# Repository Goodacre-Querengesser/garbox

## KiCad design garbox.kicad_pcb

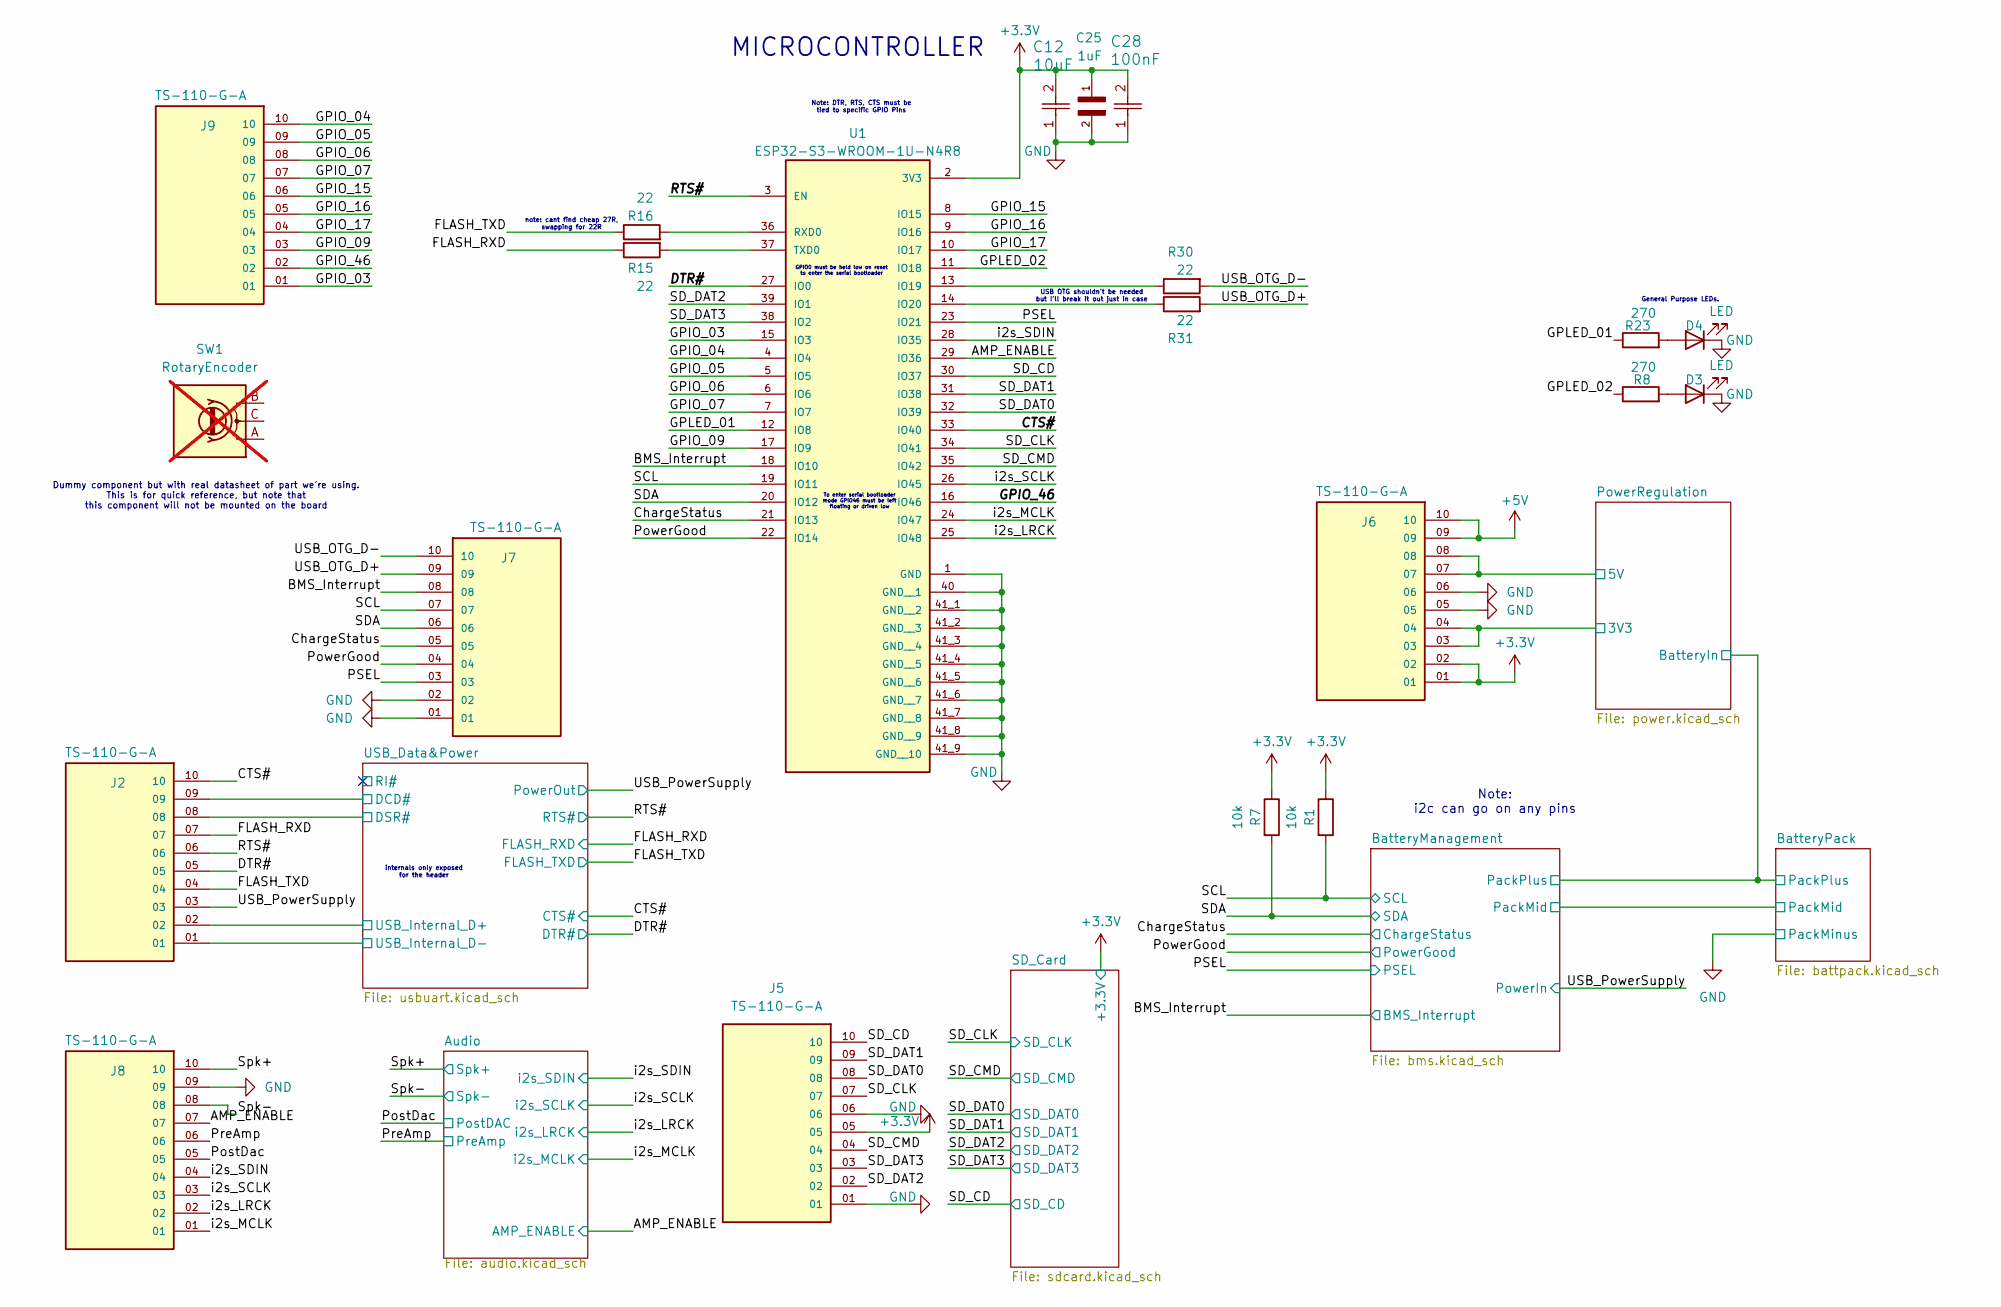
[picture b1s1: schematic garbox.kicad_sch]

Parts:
C12: 10uF; CAP_CL31_SAM; MPN C13585
C25: 1uF; CAPC3216X180N; MPN C1848
C28: 100nF; CAPC1005X55N; MPN C1525
D3, D4: LED; LED_0201_0603Metric; MPN C2286
J2, J5, J6, J7, J8, J9: TS-110-G-A; SAMTEC_TS-110-G-A; PARTREV R
R1, R7: 10k; R_0201_0603Metric; MPN C25804
R8, R23: 270; R_0201_0603Metric; MPN C22966
R15, R16, R30, R31: 22; R_0201_0603Metric; MPN C23345
SW1: RotaryEncoder; RotaryEncoder_Bourns_Horizontal_PEC09-2xxxF-Nxxxx; MPN C143788; not fitted
U1: ESP32-S3-WROOM-1U-N4R8; XCVR_ESP32-S3-WROOM-1U-N4R8; PARTREV v1.1

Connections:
+3.3V: C12.2, C25.1, C28.2, J5.05, J6.01, J6.02, R1.1, R7.1, U1.2 (3V3); also elsewhere on the board
+5V: J6.09, J6.10; also elsewhere on the board
/AMP_ENABLE: J8.07, U1.29 (IO36); also elsewhere on the board
/BMS_Interrupt: J7.08, U1.18 (IO10); also elsewhere on the board
/CTS#: J2.10, U1.33 (IO40); also elsewhere on the board
/ChargeStatus: J7.05, U1.21 (IO13); also elsewhere on the board
/DTR#: J2.05, U1.27 (IO0); also elsewhere on the board
/FLASH_RXD: J2.07, R15.1; also elsewhere on the board
/FLASH_TXD: J2.04, R16.1; also elsewhere on the board
/GPIO_03: J9.01, U1.15 (IO3)
/GPIO_04: J9.10, U1.4 (IO4)
/GPIO_05: J9.09, U1.5 (IO5)
/GPIO_06: J9.08, U1.6 (IO6)
/GPIO_07: J9.07, U1.7 (IO7)
/GPIO_09: J9.03, U1.17 (IO9)
/GPIO_15: J9.06, U1.8 (IO15)
/GPIO_16: J9.05, U1.9 (IO16)
/GPIO_17: J9.04, U1.10 (IO17)
/GPIO_46: J9.02, U1.16 (IO46)
/GPLED_01: R23.1, U1.12 (IO8)
/GPLED_02: R8.1, U1.11 (IO18)
/PSEL: J7.03, U1.23 (IO21); also elsewhere on the board
/PostDac: J8.05; also elsewhere on the board
/PowerGood: J7.04, U1.22 (IO14); also elsewhere on the board
/PowerRegulation/3V3: J6.03, J6.04; also elsewhere on the board
/PowerRegulation/5V: J6.07, J6.08; also elsewhere on the board
/PreAmp: J8.06; also elsewhere on the board
/RTS#: J2.06, U1.3 (EN); also elsewhere on the board
/SCL: J7.07, R1.2, U1.19 (IO11); also elsewhere on the board
/SDA: J7.06, R7.2, U1.20 (IO12); also elsewhere on the board
/SD_CD: J5.10, U1.30 (IO37); also elsewhere on the board
/SD_CLK: J5.07, U1.34 (IO41); also elsewhere on the board
/SD_CMD: J5.04, U1.35 (IO42); also elsewhere on the board
/SD_DAT0: J5.08, U1.32 (IO39); also elsewhere on the board
/SD_DAT1: J5.09, U1.31 (IO38); also elsewhere on the board
/SD_DAT2: J5.02, U1.39 (IO1); also elsewhere on the board
/SD_DAT3: J5.03, U1.38 (IO2); also elsewhere on the board
/Spk+: J8.10; also elsewhere on the board
/Spk-: J8.08; also elsewhere on the board
/USB_Data&Power/DCD#: J2.09; also elsewhere on the board
/USB_Data&Power/DSR#: J2.08; also elsewhere on the board
/USB_Data&Power/USB_D+: J2.02; also elsewhere on the board
/USB_Data&Power/USB_D-: J2.01; also elsewhere on the board
/USB_OTG_D+: J7.09, R31.2
/USB_OTG_D-: J7.10, R30.2
/USB_PowerSupply: J2.03; also elsewhere on the board
/i2s_LRCK: J8.02, U1.25 (IO48); also elsewhere on the board
/i2s_MCLK: J8.01, U1.24 (IO47); also elsewhere on the board
/i2s_SCLK: J8.03, U1.26 (IO45); also elsewhere on the board
/i2s_SDIN: J8.04, U1.28 (IO35); also elsewhere on the board
GND: C12.1, C25.2, C28.1, D3.1 (K), D4.1 (K), J5.01, J5.06, J6.05, J6.06, J7.01, J7.02, J8.09, U1.1 (GND), U1.40 (GND__1), U1.41_1 (GND__2), U1.41_2 (GND__3), U1.41_3 (GND__4), U1.41_4 (GND__5), U1.41_5 (GND__6), U1.41_6 (GND__7), U1.41_7 (GND__8), U1.41_8 (GND__9), U1.41_9 (GND__10), U1.41_10, U1.41_11, U1.41_12, U1.41_13, U1.41_14, U1.41_15, U1.41_16, U1.41_17, U1.41_18, U1.41_19, U1.41_20, U1.41_21; also elsewhere on the board
unnamed: D3.2 (A), R8.2
unnamed: D4.2 (A), R23.2
unnamed: R30.1, U1.13 (IO19)
unnamed: R31.1, U1.14 (IO20)
unnamed: R16.2, U1.36 (RXD0)
unnamed: R15.2, U1.37 (TXD0)

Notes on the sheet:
GPIO0 must be held low on reset to enter the serial bootloader
Note: DTR, RTS, CTS must be tied to specific GPIO Pins
internals only exposed for the header
note: cant find cheap 27R, swapping for 22R
Dummy component but with real datasheet of part we're using. This is for quick reference, but note that this component will not be mounted on the board
MICROCONTROLLER
Note: i2c can go on any pins
To enter serial bootloader mode GPIO46 must be left floating or driven low
USB OTG shouldn't be needed but I'll break it out just in case
General Purpose LEDs.

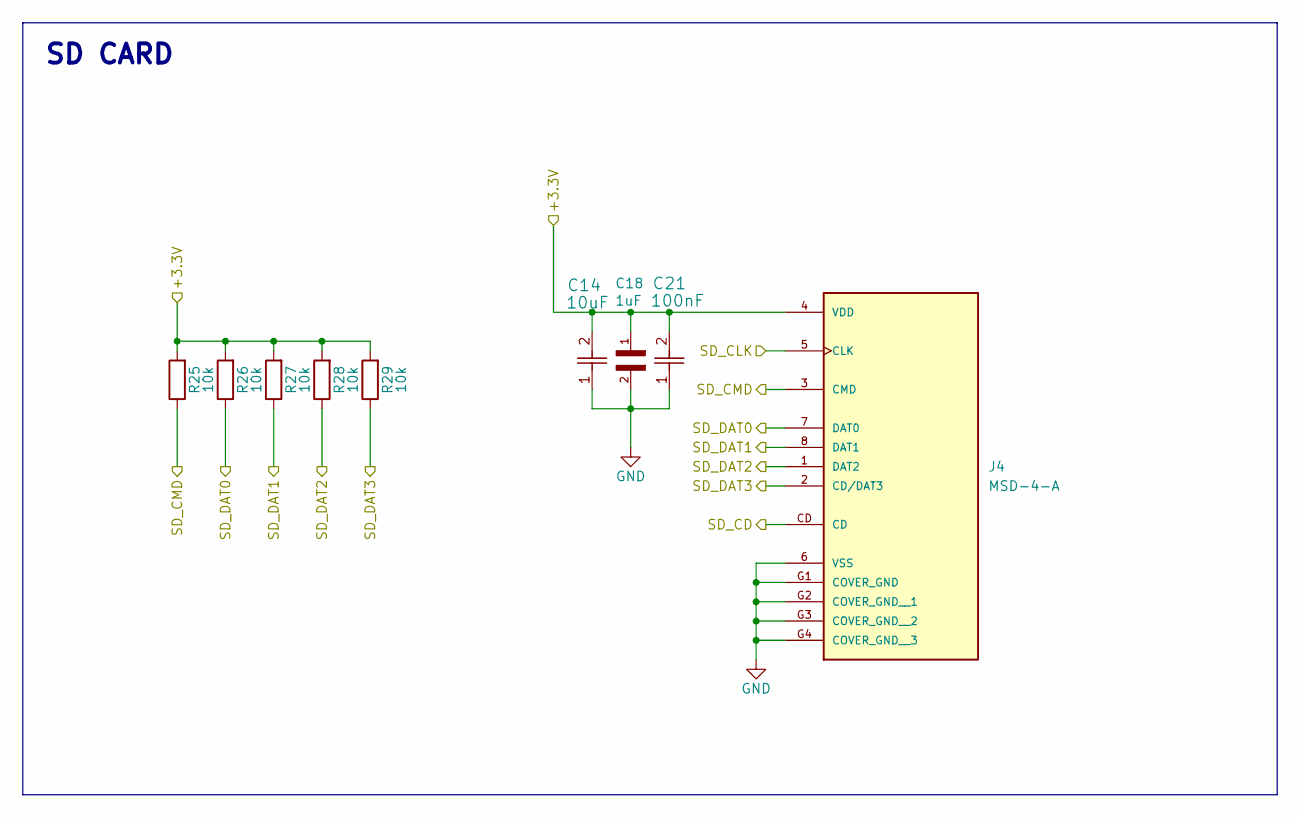
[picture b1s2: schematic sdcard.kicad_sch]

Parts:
C14: 10uF; CAP_CL31_SAM; MPN C13585
C18: 1uF; CAPC3216X180N; MPN C1848
C21: 100nF; CAPC1005X55N; MPN C1525
J4: MSD-4-A; CUI_MSD-4-A; PARTREV 1.0
R25, R26, R27, R28, R29: 10k; R_0201_0603Metric; MPN C25804

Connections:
+3.3V: C14.2, C18.1, C21.2, J4.4 (VDD), R25.2, R26.2, R27.2, R28.2, R29.2; also elsewhere on the board
/SD_CD: J4.CD; also elsewhere on the board
/SD_CLK: J4.5 (CLK); also elsewhere on the board
/SD_CMD: J4.3 (CMD), R25.1; also elsewhere on the board
/SD_DAT0: J4.7 (DAT0), R26.1; also elsewhere on the board
/SD_DAT1: J4.8 (DAT1), R27.1; also elsewhere on the board
/SD_DAT2: J4.1 (DAT2), R28.1; also elsewhere on the board
/SD_DAT3: J4.2 (CD/DAT3), R29.1; also elsewhere on the board
GND: C14.1, C18.2, C21.1, J4.6 (VSS), J4.G1 (COVER_GND), J4.G2 (COVER_GND__1), J4.G3 (COVER_GND__2), J4.G4 (COVER_GND__3); also elsewhere on the board

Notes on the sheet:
SD CARD

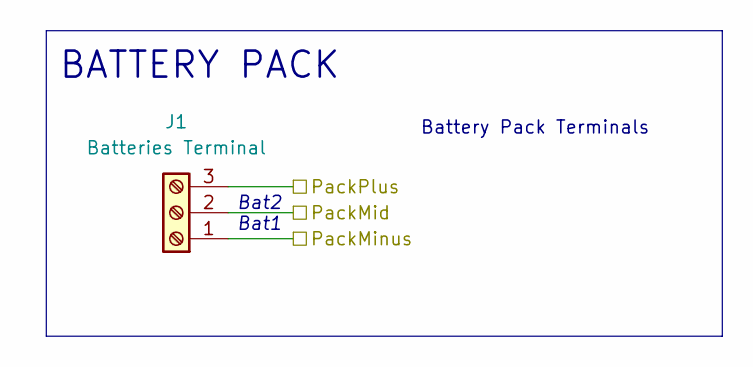
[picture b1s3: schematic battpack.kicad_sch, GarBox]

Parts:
J1: Batteries Terminal; TerminalBlock_bornier-3_P5.08mm

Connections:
/BatteryManagement/PackMid: J1.2; also elsewhere on the board
/BatteryManagement/PackPlus: J1.3; also elsewhere on the board
GND: J1.1; also elsewhere on the board

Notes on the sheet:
Battery Pack Terminals
BATTERY PACK
Bat2 Bat1

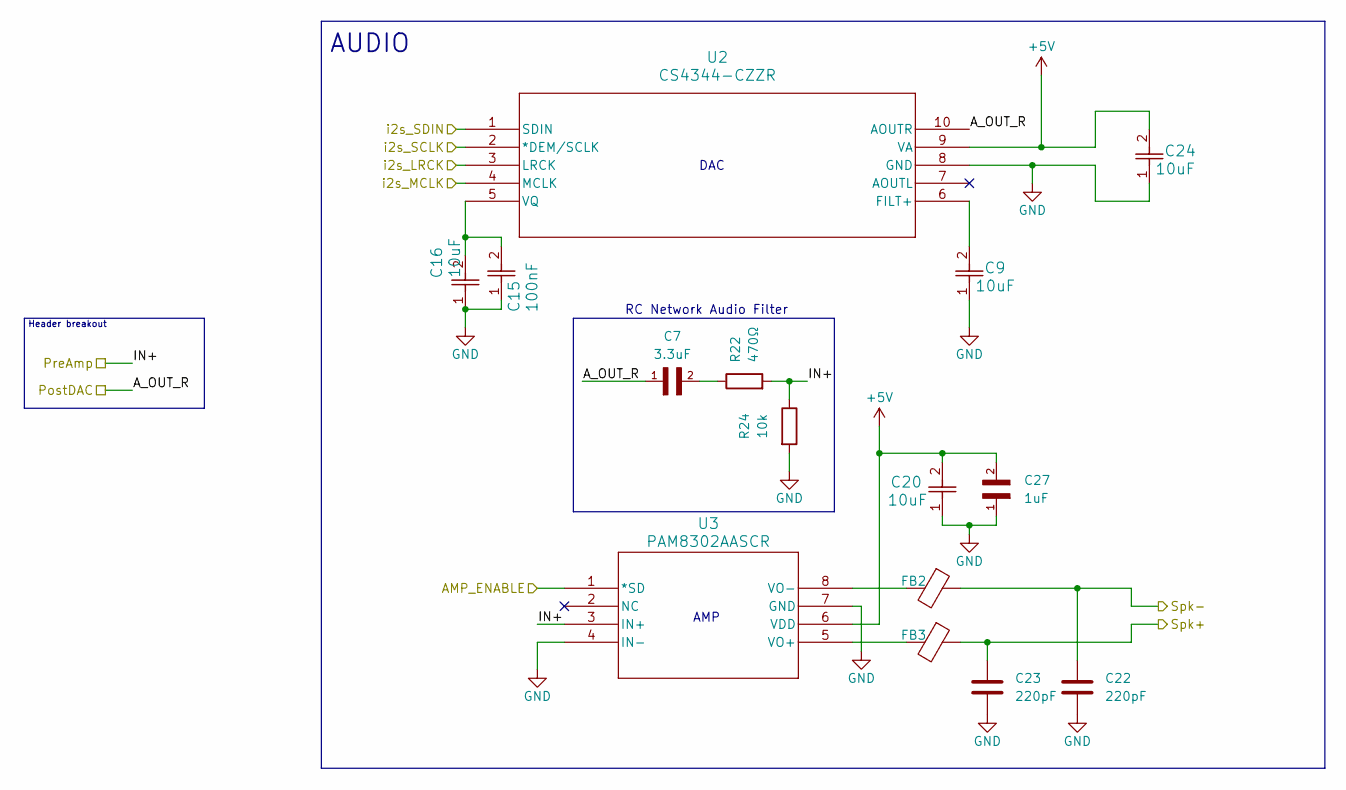
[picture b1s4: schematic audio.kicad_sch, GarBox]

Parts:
C7: 3.3uF; CAPC1608X90N; MPN C51412
C9, C16, C20, C24: 10uF; CAP_CL31_SAM; MPN C13585
C15: 100nF; CAPC1005X55N; MPN C1525
C22, C23: 220pF; C_0201_0603Metric; MPN C1603
C27: 1uF; CAPC3216X180N; MPN C1848
FB2, FB3: GZ1608D601TF; L_Sunlord_MWSA0603S; MPN C1002
R22: 470Ω; R_0603_1608Metric; MPN C23179
R24: 10k; R_0201_0603Metric; MPN C25804
U2: CS4344-CZZR; CIR_3TSSOP-10; MPN C2895053
U3: PAM8302AASCR; PAM8302AASCR_DIO; MPN C113367

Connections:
+5V: C20.2, C24.2, C27.2, U2.9 (VA), U3.6 (VDD); also elsewhere on the board
/AMP_ENABLE: U3.1 (*SD); also elsewhere on the board
/PostDac: C7.1, U2.10 (AOUTR); also elsewhere on the board
/PreAmp: R22.2, R24.1, U3.3 (IN+); also elsewhere on the board
/Spk+: C23.1, FB3.1; also elsewhere on the board
/Spk-: C22.1, FB2.1; also elsewhere on the board
/i2s_LRCK: U2.3 (LRCK); also elsewhere on the board
/i2s_MCLK: U2.4 (MCLK); also elsewhere on the board
/i2s_SCLK: U2.2 (*DEM/SCLK); also elsewhere on the board
/i2s_SDIN: U2.1 (SDIN); also elsewhere on the board
GND: C9.1, C15.1, C16.1, C20.1, C22.2, C23.2, C24.1, C27.1, R24.2, U2.8 (GND), U3.4 (IN-), U3.7 (GND); also elsewhere on the board
unnamed: C7.2, R22.1
unnamed: C9.2, U2.6 (FILT+)
unnamed: C15.2, C16.2, U2.5 (VQ)
unnamed: FB3.2, U3.5 (VO+)
unnamed: FB2.2, U3.8 (VO-)

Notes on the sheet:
AUDIO
Header breakout
AMP
DAC
RC Network Audio Filter

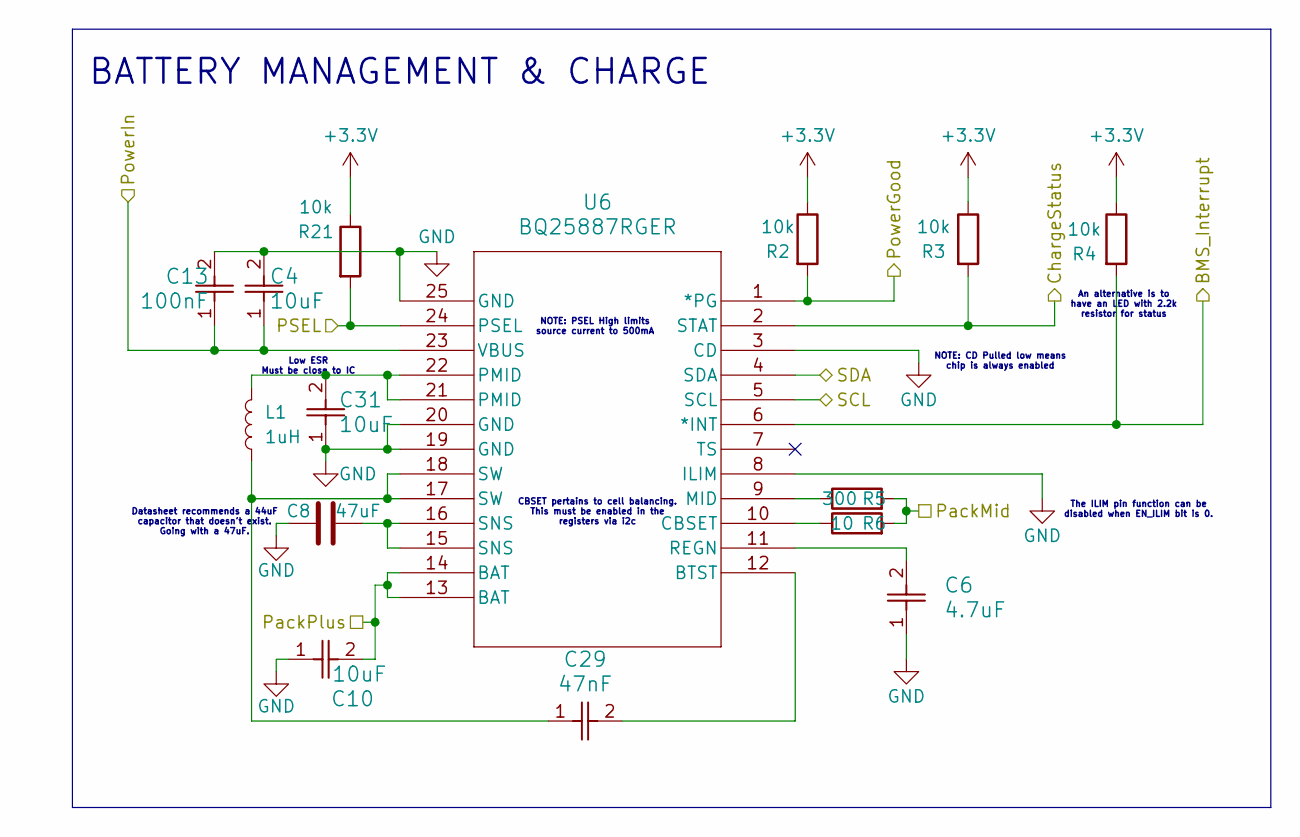
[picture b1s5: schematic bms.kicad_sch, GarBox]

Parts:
C4, C31: 10uF; CAP_CL21_SAM; MPN C15850
C6: 4.7uF; C_0805_2012Metric; MPN C1779
C8: 47uF; C_1206_3216Metric; MPN C96123
C10: 10uF; CAP_CL31_SAM; MPN C13585
C13: 100nF; CAPC1005X55N; MPN C1525
C29: 47nF; CAP_CL10_SAM; MPN C1622
L1: 1uH; L_Wuerth_WE-GF-1210; MPN C439775
R2, R3, R4, R21: 10k; R_0201_0603Metric; MPN C25804
R5: 300; R_0201_0603Metric; MPN C23025
R6: 10; R_2512_6332Metric; MPN C16861
U6: BQ25887RGER; VQFN24_RGE_TEX; MPN C2761614

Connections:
+3.3V: R2.1, R3.1, R4.1, R21.1; also elsewhere on the board
/BMS_Interrupt: R4.2, U6.6 (*INT); also elsewhere on the board
/BatteryManagement/PackMid: R5.2, R6.2; also elsewhere on the board
/BatteryManagement/PackPlus: C10.2, U6.13 (BAT), U6.14 (BAT); also elsewhere on the board
/ChargeStatus: R3.2, U6.2 (STAT); also elsewhere on the board
/PSEL: R21.2, U6.24 (PSEL); also elsewhere on the board
/PowerGood: R2.2, U6.1 (*PG); also elsewhere on the board
/SCL: U6.5 (SCL); also elsewhere on the board
/SDA: U6.4 (SDA); also elsewhere on the board
/USB_PowerSupply: C4.1, C13.1, U6.23 (VBUS); also elsewhere on the board
GND: C4.2, C6.1, C8.2, C10.1, C13.2, C31.1, U6.3 (CD), U6.8 (ILIM), U6.19 (GND), U6.20 (GND), U6.25 (GND); also elsewhere on the board
unnamed: C8.1, U6.15 (SNS), U6.16 (SNS)
unnamed: C29.1, L1.1, U6.17 (SW), U6.18 (SW)
unnamed: C31.2, L1.2, U6.21 (PMID), U6.22 (PMID)
unnamed: C29.2, U6.12 (BTST)
unnamed: R6.1, U6.10 (CBSET)
unnamed: R5.1, U6.9 (MID)
unnamed: C6.2, U6.11 (REGN)

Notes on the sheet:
BATTERY MANAGEMENT & CHARGE
NOTE: CD Pulled low means chip is always enabled
CBSET pertains to cell balancing. This must be enabled in the registers via i2c
Datasheet recommends a 44uF capacitor that doesn't exist. Going with a 47uF.
NOTE: PSEL High limits source current to 500mA
Low ESR Must be close to IC
An alternative is to have an LED with 2.2k resistor for status
The ILIM pin function can be disabled when EN_ILIM bit is 0.

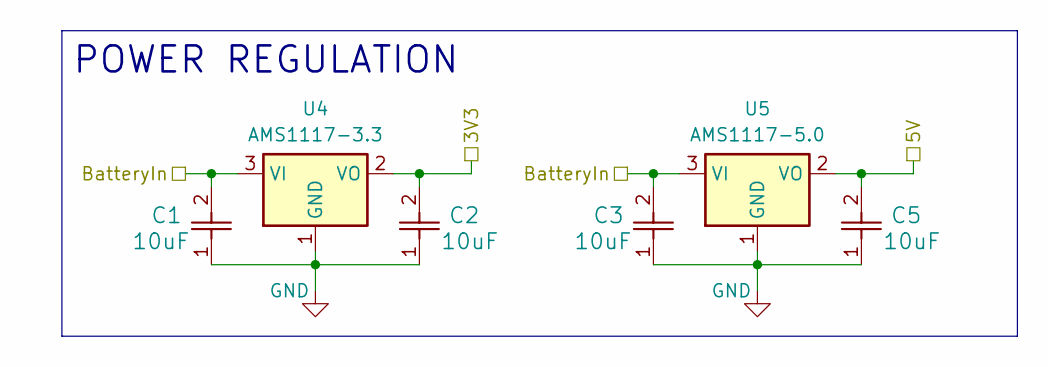
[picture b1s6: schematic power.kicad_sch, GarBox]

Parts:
C1, C2, C3, C5: 10uF; CAP_CL31_SAM; MPN C13585
U4: AMS1117-3.3; SOT-223-3_TabPin2; MPN C6186
U5: AMS1117-5.0; SOT-223-3_TabPin2; MPN C6187

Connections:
/BatteryManagement/PackPlus: C1.2, C3.2, U4.3 (VI), U5.3 (VI); also elsewhere on the board
/PowerRegulation/3V3: C2.2, U4.2 (VO); also elsewhere on the board
/PowerRegulation/5V: C5.2, U5.2 (VO); also elsewhere on the board
GND: C1.1, C2.1, C3.1, C5.1, U4.1 (GND), U5.1 (GND); also elsewhere on the board

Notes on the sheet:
POWER REGULATION

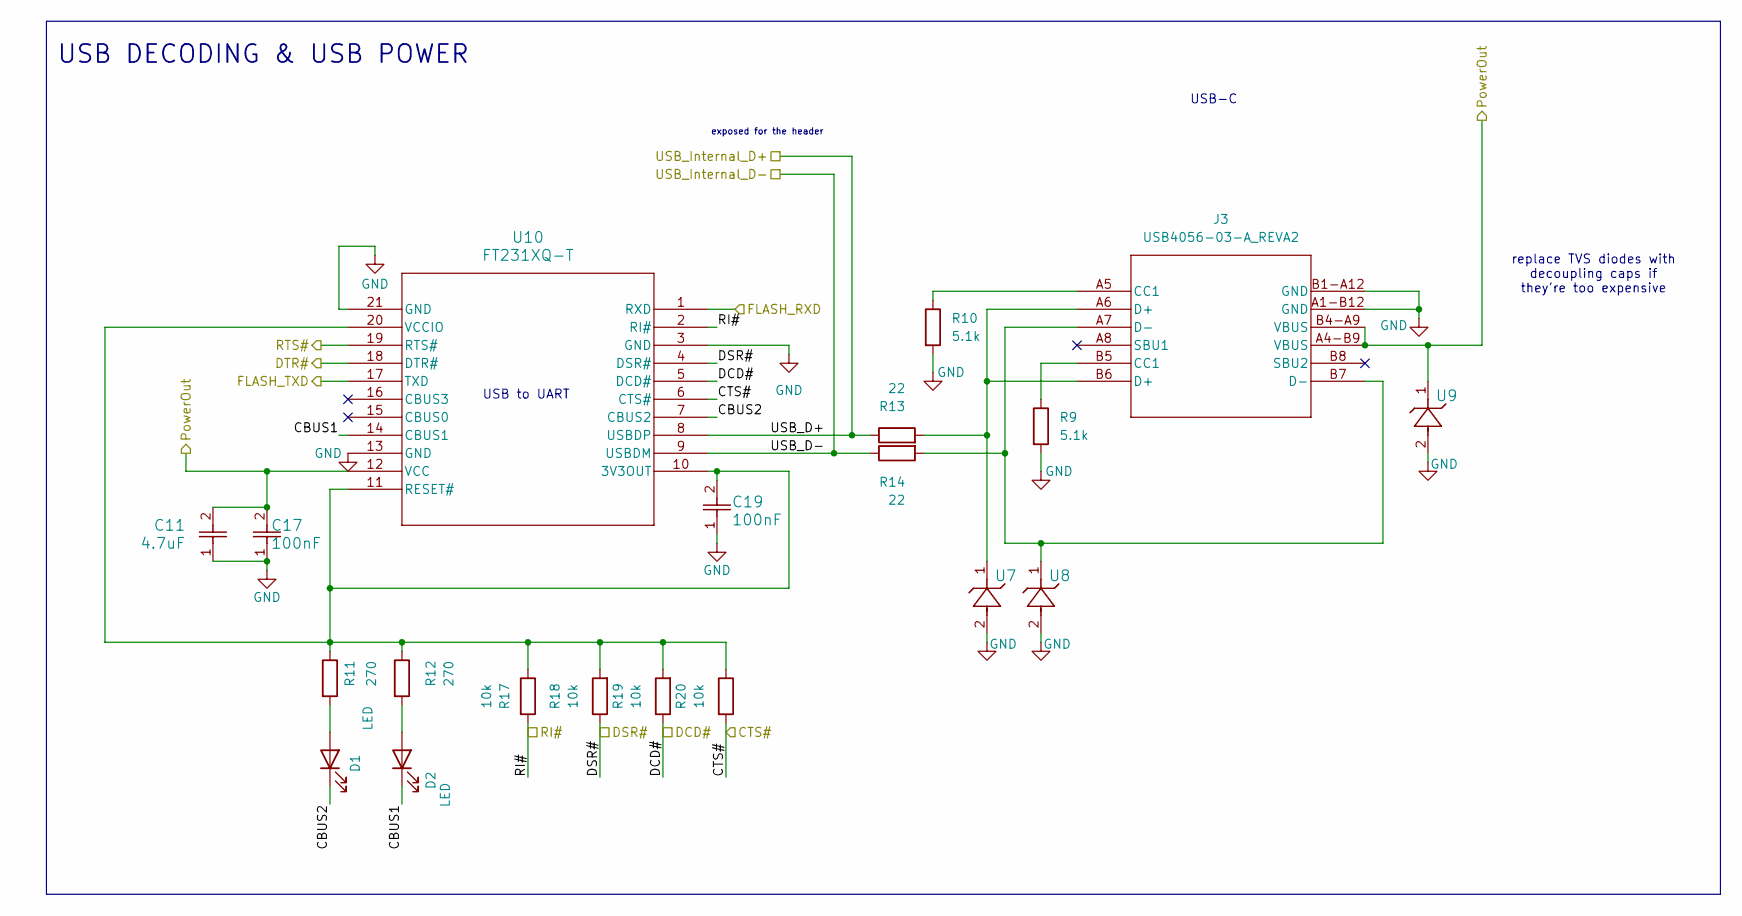
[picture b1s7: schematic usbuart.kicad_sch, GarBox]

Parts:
C11: 4.7uF; C_0805_2012Metric; MPN C1779
C17, C19: 100nF; CAPC1005X55N; MPN C1525
D1, D2: LED; LED_0201_0603Metric; MPN C2286
J3: USB4056-03-A_REVA2; 12402012E212A_AMP; PARTREV A2
R9, R10: 5.1k; R_0201_0603Metric; MPN C23186
R11, R12: 270; R_0201_0603Metric; MPN C22966
R13, R14: 22; R_0201_0603Metric; MPN C23345
R17, R18, R19, R20: 10k; R_0201_0603Metric; MPN C25804
U7, U8, U9: CPDQ5V0-HF; CPDQ; MPN C2441615
U10: FT231XQ-T; QFN20_FT231XQ_FTD; MPN C1521552

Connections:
/CTS#: R20.2, U10.6 (CTS#); also elsewhere on the board
/DTR#: U10.18 (DTR#); also elsewhere on the board
/FLASH_RXD: U10.1 (RXD); also elsewhere on the board
/FLASH_TXD: U10.17 (TXD); also elsewhere on the board
/RTS#: U10.19 (RTS#); also elsewhere on the board
/USB_Data&Power/CBUS1: D2.1 (K), U10.14 (CBUS1)
/USB_Data&Power/CBUS2: D1.1 (K), U10.7 (CBUS2)
/USB_Data&Power/DCD#: R19.1, U10.5 (DCD#); also elsewhere on the board
/USB_Data&Power/DSR#: R18.1, U10.4 (DSR#); also elsewhere on the board
/USB_Data&Power/RI#: R17.2, U10.2 (RI#)
/USB_Data&Power/USB_D+: R13.1, U10.8 (USBDP); also elsewhere on the board
/USB_Data&Power/USB_D-: R14.1, U10.9 (USBDM); also elsewhere on the board
/USB_PowerSupply: C11.2, C17.2, J3.A4-B9 (VBUS), J3.B4-A9 (VBUS), U9.1, U10.12 (VCC); also elsewhere on the board
GND: C11.1, C17.1, C19.1, J3.A1-B12 (GND), J3.B1-A12 (GND), R9.2, R10.2, U7.2, U8.2, U9.2, U10.3 (GND), U10.13 (GND), U10.21 (GND); also elsewhere on the board
unnamed: D1.2 (A), R11.2
unnamed: D2.2 (A), R12.2
unnamed: J3.A5 (CC1), R10.1
unnamed: J3.B5 (CC1), R9.1
unnamed: J3.A6 (D+), J3.B6 (D+), R13.2, U7.1
unnamed: J3.A7 (D-), J3.B7 (D-), R14.2, U8.1
unnamed: C19.2, R11.1, R12.1, R17.1, R18.2, R19.2, R20.1, U10.10 (3V3OUT), U10.11 (RESET#), U10.20 (VCCIO)

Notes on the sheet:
replace TVS diodes with decoupling caps if they're too expensive
exposed for the header
USB to UART
USB-C
USB DECODING & USB POWER

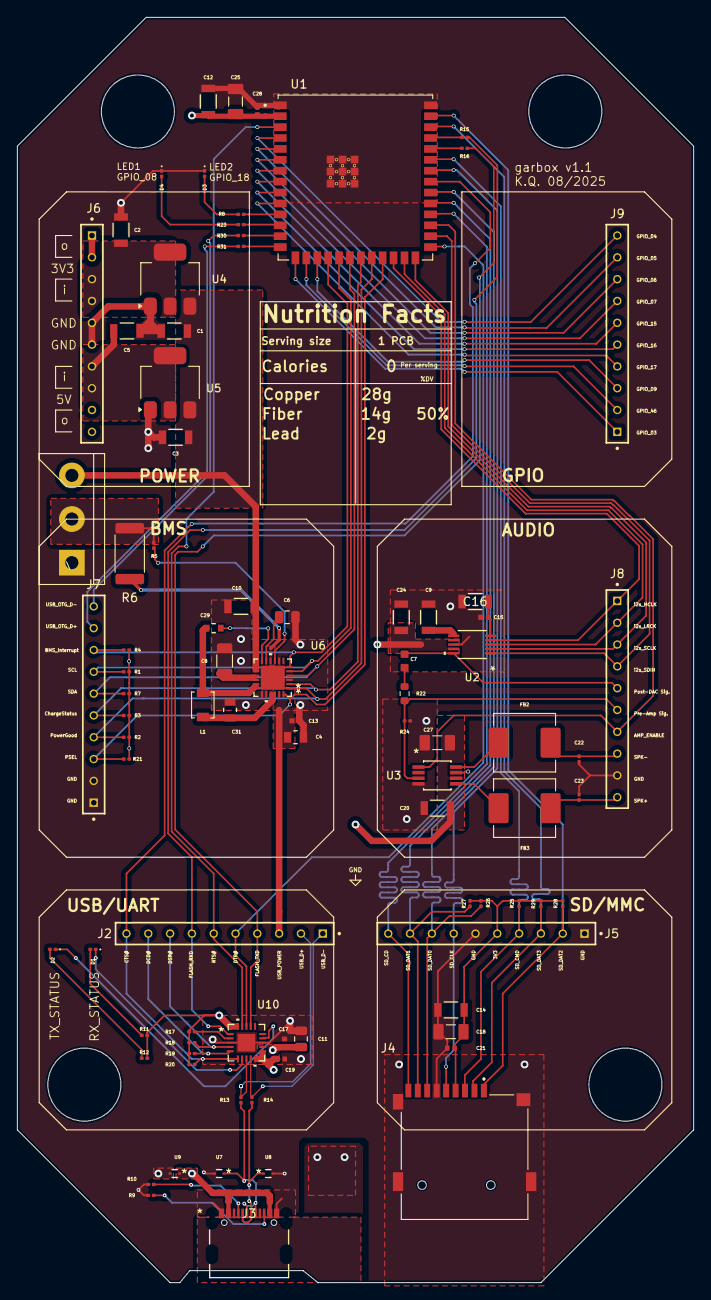
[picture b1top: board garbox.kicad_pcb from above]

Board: 4 copper layers, 78.7 x 147.3 mm, 86 parts (0 on the bottom side), 81 nets.

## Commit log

2025-08-22 added headers, cleaned up main schematic and now replanning board layout
2025-08-22 meant to put these in the last commit
2025-08-23 Finished preliminary routing of v1.1 of the board
2025-08-23 Cleaned up silkscreen and finished routing
2025-08-27 fixed incorrect gpio and added silkscreen funny
2025-08-27 assigned 3d models to footprints
2025-08-27 fixed usb clearance, added ground plane to top and bottom
2025-10-17 designated MPN parts from JLC library
2025-11-14 Updated part numbers
2025-11-28 swapped esp32-s3-wroom-1-n4r8 for esp32-s3-wroom-1u-n4r8 board, fixed unconnected net on USB connector, and tidied up some traces on usb.
2025-11-29 changed minimum hole/diameter size to 0.2mm/0.45mm for manufacturer compliance. moved some traces around to avoid DRC errors accordingly
